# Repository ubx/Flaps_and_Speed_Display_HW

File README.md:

# Flaps & Speed

A KiCad project for a hardware module designed to interface with flap and speed sensors, likely for aviation or automotive applications.

## Features
- **CAN Bus Communication:** Includes CAN-In and CAN-Out interfaces using the SN65HVD230 transceiver.
- **Connectors:** Utilizes M12 5-pin connectors for reliable external connections.
- **Power:** Designed for 12V input with onboard 3.3V regulation, [Micro BEC SE-0509](https://de.aliexpress.com/item/1005010499841098.html?spm=a2g0o.order_list.order_list_main.4.743e1802VIZ0pe&gatewayAdapt=glo2deu)
- **Display:** Connected (H7-H14) to a [ESP32-S3-Touch-AMOLED-1.75](https://de.aliexpress.com/item/1005008989323572.html?spm=a2g0o.order_list.order_list_main.206.743e1802VIZ0pe&gatewayAdapt=glo2deu), [Wiki](https://www.waveshare.com/wiki/ESP32-S3-Touch-AMOLED-1.75)

## Software

This hardware module is designed to run the following software:
[Flaps and Speed Display](https://github.com/ubx/Flaps_and_Speed_Display)

## Todo
- [x] Review PCB toward a more professional layout
- [x] Crate a PCBWay ready BOM
- [ ] Add more professional displays connector
- [ ] Test kicad-happy ???

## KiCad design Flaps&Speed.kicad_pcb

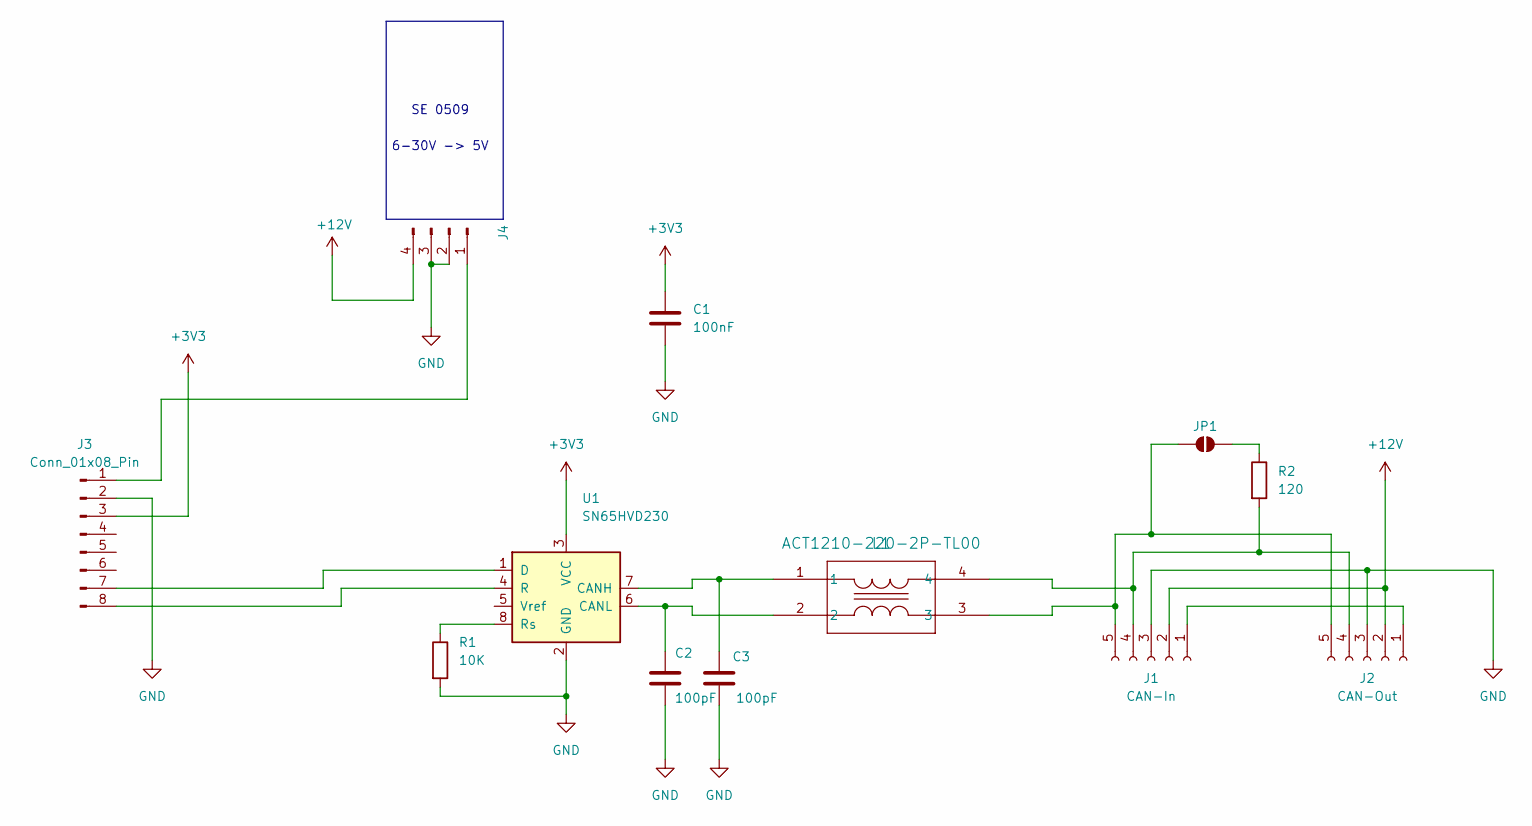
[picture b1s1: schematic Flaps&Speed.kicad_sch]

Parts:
C1: 100nF; R_1206_3216Metric_Pad1.30x1.75mm_HandSolder; MPN GRM31CR71H104KA01L
C2, C3: 100pF; R_1206_3216Metric_Pad1.30x1.75mm_HandSolder; MPN GRM31C5C1H101JA01L
J1: CAN-In; M12_A_5pin_Male_PCD5_Drill1p2
J2: CAN-Out; M12_A_5pin_Male_PCD5_Drill1p2
J3: Conn_01x08_Pin; PinSocket_1x08_P2.54mm_Vertical
J4: Conn_01x04_Pin; PinSocket_1x04_P2.54mm_Vertical
JP1: SolderJumper_2_Open; SolderJumper-2_P1.3mm_Open_TrianglePad1.0x1.5mm
L1: ACT1210-220-2P-TL00; ACT1210_TDK; MPN ACT1210-220-2P-TL00
R1: 10K; R_1206_3216Metric_Pad1.30x1.75mm_HandSolder; MPN RC1206FR-0710KL
R2: 120; R_1206_3216Metric_Pad1.30x1.75mm_HandSolder; MPN RC1206FR-07120RL
U1: SN65HVD230; SOIC-8_3.9x4.9mm_P1.27mm; MPN SN65HVD230DR

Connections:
+3V3: C1.1, J3.3, U1.3 (VCC)
+12V: J1.2, J2.2, J4.4
GND: C1.2, C2.2, C3.2, J1.3, J2.3, J3.2, J4.2, J4.3, R1.2, U1.2 (GND)
unnamed: J1.1, J2.1
unnamed: J1.4, J2.4, L1.4, R2.2
unnamed: J1.5, J2.5, JP1.1 (A), L1.3
unnamed: J3.1, J4.1
unnamed: J3.7, U1.1 (D)
unnamed: J3.8, U1.4 (R)
unnamed: JP1.2 (B), R2.1
unnamed: C3.1, L1.1, U1.7 (CANH)
unnamed: C2.1, L1.2, U1.6 (CANL)
unnamed: R1.1, U1.8 (Rs)

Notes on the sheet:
SE 0509
6-30V -> 5V

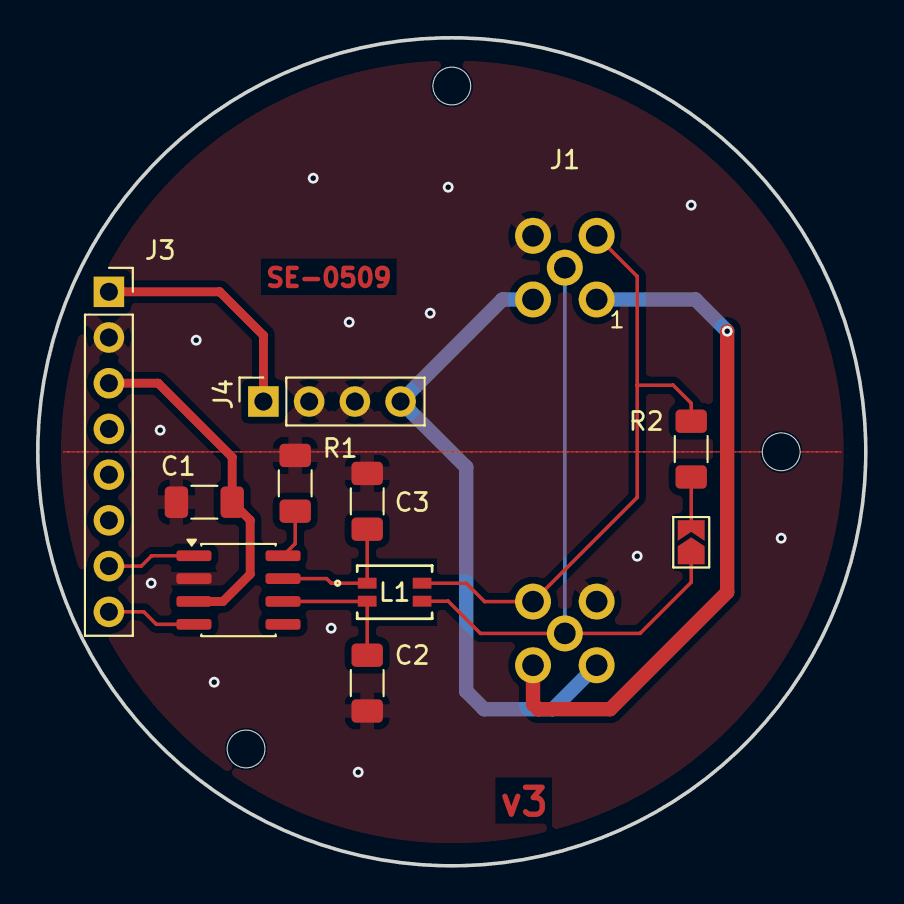
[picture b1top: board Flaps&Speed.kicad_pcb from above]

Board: 2 copper layers, 46.0 x 46.0 mm, 15 parts (1 on the bottom side), 13 nets.

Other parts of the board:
MH1, MH2, MH3: MountingHole_2.1mm

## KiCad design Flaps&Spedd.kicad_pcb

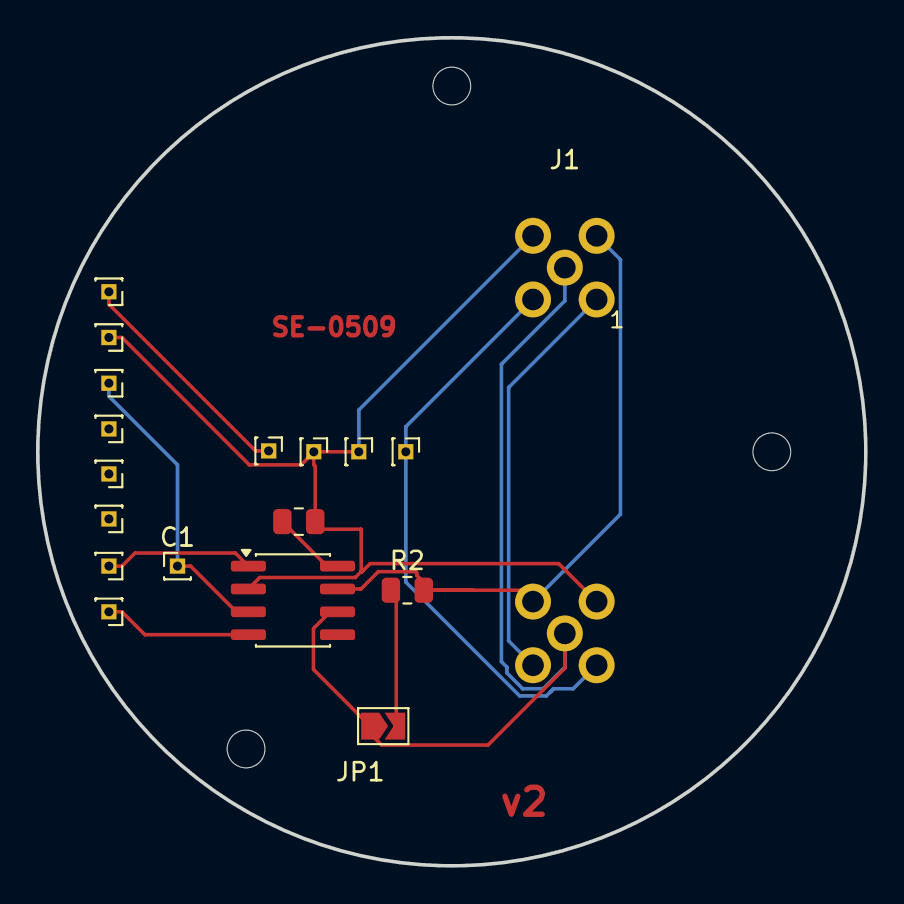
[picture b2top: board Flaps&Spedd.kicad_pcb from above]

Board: 2 copper layers, 46.0 x 46.0 mm, 22 parts (1 on the bottom side), 11 nets.

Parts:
C1: 100nF; PinHeader_1x01_P1.00mm_Vertical
H1: 5V; PinHeader_1x01_P1.00mm_Vertical
H2, H3: GND; PinHeader_1x01_P1.00mm_Vertical
H4: 12V; PinHeader_1x01_P1.00mm_Vertical
H7, H8, H9, H10, H11, H12, H13, H14: 1; PinHeader_1x01_P1.00mm_Vertical
J1: CAN-M; M12_A_5pin_Male_PCD5_Drill1p2
J2: CAN-F; M12_A_5pin_Male_PCD5_Drill1p2
JP1: SolderJumper_2_Open; SolderJumper-2_P1.3mm_Open_TrianglePad1.0x1.5mm
MH1, MH2, MH3: MountingHole_2.1mm
R1: 10K; R_0805_2012Metric
R2: 120; R_0805_2012Metric
U1: SN65HVD230; SOIC-8_3.9x4.9mm_P1.27mm

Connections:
+3V3: C1.1, H9.1, U1.3 (VCC)
+12V: H4.1, J1.2, J2.2
GND: H2.1, H3.1, H8.1, J1.3, J2.3, R1.2, U1.2 (GND)
unnamed: H1.1, H7.1
unnamed: J1.1, J2.1
unnamed: J1.4, J2.4, R2.2, U1.7 (CANH)
unnamed: J1.5, J2.5, JP1.1 (A), U1.6 (CANL)
unnamed: JP1.2 (B), R2.1
unnamed: H14.1, U1.1 (D)
unnamed: H13.1, U1.4 (R)
unnamed: R1.1, U1.8 (Rs)

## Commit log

2026-03-06 Initial.
2026-03-06 Label moved.
2026-03-09 Change to PinHeader_1x01_P1.27mm_Vertical, add C1.
2026-03-09 Initial
2026-03-11 Wrong CAN connector placement, mirrored!
2026-04-13 Add comment.
2026-04-14 Fix: - Löcher Kontakte zu klein - DC Wandler Vin (12V) und Vout (5V) vertauscht - DC Wandler mehr zu Mitte - Widerstände und Kondensator anders Format
2026-04-15 Remove unused track on F.Cu layer.
2026-04-19 Add README with project overview and features.
2026-04-19 Update README: add Waveshare Wiki link for ESP32-S3-Touch-AMOLED-1.75 display
2026-04-21 Add GNU General Public License v3
2026-04-22 Add GitHub Actions workflow for KiCad design reviews
2026-04-22 Enable manual trigger for KiCad design review workflow
2026-04-22 Update KiCad review workflow: switch to fork for power rail fix
2026-04-23 Revert "Update KiCad review workflow: switch to fork for power rail fix"
    This reverts commit bd045310696c16846bc347357ebf91971971c967.
    Due to the fix in commit 8bdef04633a99cd4ed570945c9695ed741ce7798.
2026-04-26 Add initial KiCad project files for "Flaps&Spedd" schematic and PCB
2026-05-03 Reapply "Update KiCad review workflow: switch to fork for power rail fix"
    This reverts commit c969e05315677aa3a7d3b74d35de44598b77a24d.
2026-05-04 Fix typo in project file names: rename "Flaps&Spedd" to "Flaps&Speed" across all KiCad files.
2026-05-04 Adjust BOM settings and properties in KiCad project: updated field orders, added new properties, and fixed naming errors (e.g., "Flaps&Spedd" to "Flaps&Speed").
2026-05-07 Add LCSC properties to components and exclude specific through-hole parts from BOM
2026-06-05 README: Mark PCB review as complete in todo list.
